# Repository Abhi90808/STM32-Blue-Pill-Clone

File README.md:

# STM32 Blue Pill Clone

A custom recreation of the popular STM32F103C8T6 "Blue Pill" ARM Cortex-M3 development board, designed in KiCad 8 with improved layout, better decoupling, and optional USB support.

---

## Features
- STM32F103C8T6 ARM Cortex-M3 MCU @ up to 72MHz
- Onboard 8MHz crystal + 32.768kHz RTC crystal
- USB Full-Speed port (12Mbit/s)
- SWD debug/programming header
- Boot0/Boot1 jumpers
- All 37 GPIO pins broken out
- 3.3V LDO onboard
- Improved power decoupling vs original Blue Pill

## Specifications

| Parameter | Value |
|-----------|-------|
| MCU | STM32F103C8T6 |
| Core | ARM Cortex-M3 |
| Clock Speed | Up to 72MHz |
| Operating Voltage | 3.3V |
| USB Input | 5V via Micro USB |
| Flash Memory | 64KB |
| SRAM | 20KB |
| GPIO Pins | 37 |
| ADC Channels | 10 (12-bit) |
| PCB Layers | 2 |
| Designed With | KiCad 8 |

## Project Structure

```
├── Schematic/       # KiCad schematic (.kicad_sch, PDF)
├── PCB/             # PCB layout (.kicad_pcb, .kicad_pro)
├── Gerbers/         # Fabrication files
├── BOM/             # Bill of materials (CSV)
├── 3D/              # 3D model (.step)
└── Images/          # PCB renders and schematic screenshots
```

## How It Works

The STM32F103C8T6 is clocked by an 8MHz external crystal, which the internal PLL multiplies to 72MHz. Programming is done via the SWD header using ST-Link V2. The USB port supports DFU bootloader flashing without an external programmer.

## Programming Options

| Method | Tool |
|--------|------|
| SWD | ST-Link V2 + STM32CubeIDE / OpenOCD |
| USB DFU | STM32CubeProgrammer (Boot0 = 1) |
| Serial | UART1 + STM32CubeProgrammer (Boot0 = 1) |
| Arduino | Arduino IDE + STM32duino core |

## Bill of Materials (Summary)

| Component | Value | Qty |
|-----------|-------|-----|
| MCU | STM32F103C8T6 | 1 |
| Crystal | 8MHz | 1 |
| RTC Crystal | 32.768kHz | 1 |
| LDO Regulator | AMS1117-3.3V | 1 |
| USB Connector | Micro-B | 1 |
| SWD Header | 4-pin, 2.54mm | 1 |
| Decoupling Caps | 100nF | 8 |

## Fabrication

Gerber files are in `/Gerbers`, ready for JLCPCB, PCBWay, or similar.

## License

This project is licensed under the [CERN Open Hardware Licence Version 2 - Strongly Reciprocal (CERN OHL-S v2)](https://ohwr.org/cern_ohl_s_v2.txt).

## Author

**Abhi90808** — [GitHub Profile](https://github.com/Abhi90808)

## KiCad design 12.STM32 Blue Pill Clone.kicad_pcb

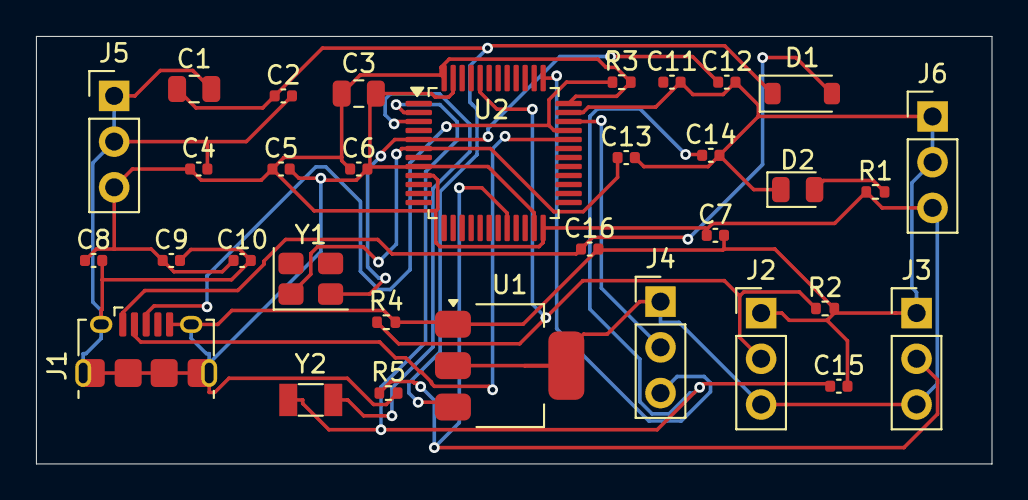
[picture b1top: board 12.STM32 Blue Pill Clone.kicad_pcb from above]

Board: 2 copper layers, 53.1 x 23.7 mm, 33 parts (0 on the bottom side), 15 nets.

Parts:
C1, C3: 10uF; C_0805_2012Metric
C2, C4, C16: 100nF; C_0402_1005Metric
C5, C6, C7, C8, C9: 100nf; C_0402_1005Metric
C10, C11: 1uf; C_0402_1005Metric
C12, C13: 20PF; C_0402_1005Metric
C14, C15: 12.5pF; C_0402_1005Metric
D1: 1N5819; D_SOD-123
D2: PWR_LED; LED_0805_2012Metric
J1: USB_B_Micro; USB_Micro-B_Amphenol_10118194_Horizontal
J2: BOOT0_SEL; PinHeader_1x03_P2.54mm_Vertical
J3: BOOT1_SEL; PinHeader_1x03_P2.54mm_Vertical
J4: SWD; PinHeader_1x03_P2.54mm_Vertical
J5: LEFT_HEADER; PinHeader_1x03_P2.54mm_Vertical
J6: RIGHT_HEADER; PinHeader_1x03_P2.54mm_Vertical
R1: 1k; R_0402_1005Metric
R2, R4, R5: 10k; R_0402_1005Metric
R3: 1.5K; R_0402_1005Metric
U1: AMS1117-3.3; SOT-223-3_TabPin2
U2: STM32F103C8T6; LQFP-48_7x7mm_P0.5mm
Y1: 8MHz; Crystal_SMD_3225-4Pin_3.2x2.5mm
Y2: 32.768kHz; Crystal_SMD_3215-2Pin_3.2x1.5mm

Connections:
+3V3: C3.1, C4.1, C5.1, C6.1, C7.1, C8.1, C9.1, C10.1, J2.3, J3.3, J4.1, J5.3, J6.3, R1.1, R3.2, U1.2 (VO), U2.9 (VDDA), U2.24 (VDD), U2.36 (VDD), U2.48 (VDD)
/ OSC32_IN: C14.1, C15.1, U2.2 (PC13), Y2.2
/BOOT0: J2.2, R2.1, R4.1, U2.44 (BOOT0)
/BOOT1: J3.2, R5.1, U2.20 (PB2)
/OSC32_OUT: U2.3 (PC14), Y2.1
/OSC_IN: C12.1, U2.5 (PD0), Y1.2
/OSC_OUT: C13.1, U2.6 (PD1), Y1.1
/SWCLK: J4.3, U2.37 (PA14)
/SWDIO: J4.2, U2.34 (PA13)
/USB_DM: J1.2 (D-), U2.32 (PA11)
/USB_DP: J1.3 (D+), R3.1, U2.33 (PA12)
/VBUS: C16.1, D1.2 (A), J1.1 (VBUS)
/VBUS_PROT: C1.1, C2.1, D1.1 (K), U1.3 (VI)
GND: C1.2, C2.2, C3.2, C4.2, C5.2, C6.2, C7.2, C8.2, C9.2, C10.2, C11.2, C12.2, C13.2, C14.2, C15.2, C16.2, D2.1 (K), J1.5 (GND), J1.6 (Shield), J2.1, J3.1, J5.1, J5.2, J6.1, J6.2, R2.2, R4.2, R5.2, U1.1 (GND), U2.8 (VSSA), U2.23 (VSS), U2.35 (VSS), U2.47 (VSS)
unnamed: D2.2 (A), R1.2
